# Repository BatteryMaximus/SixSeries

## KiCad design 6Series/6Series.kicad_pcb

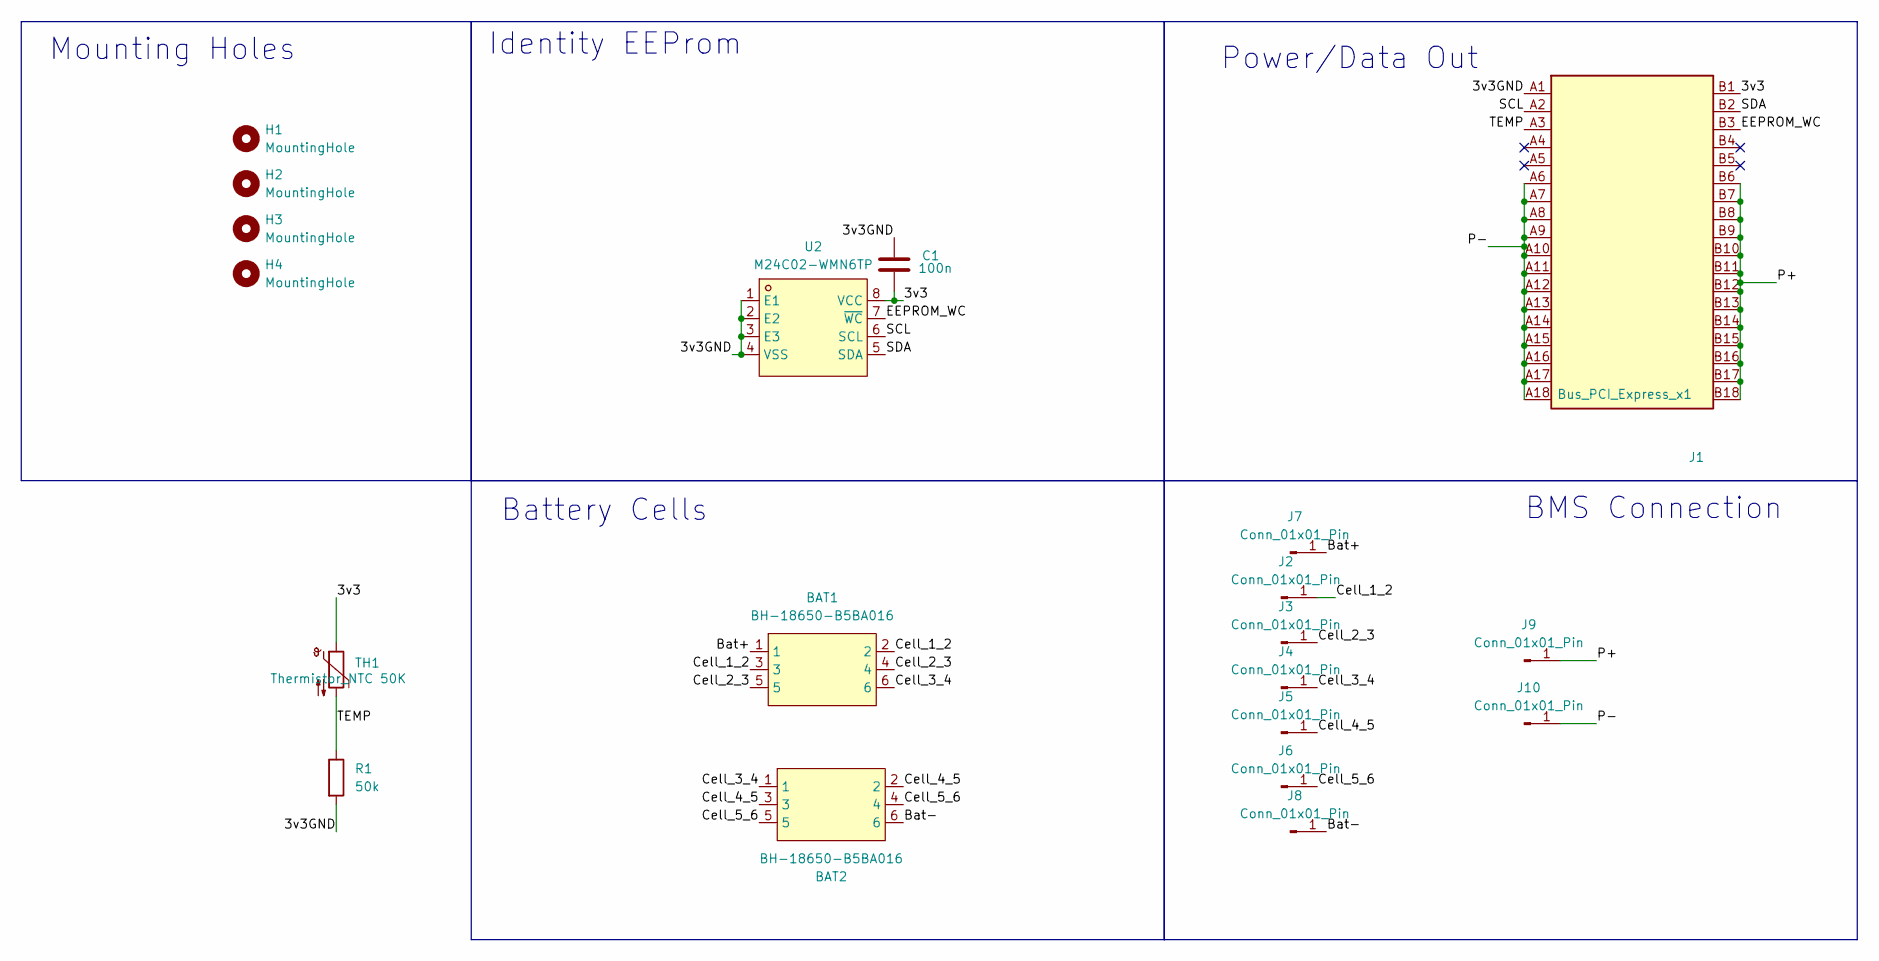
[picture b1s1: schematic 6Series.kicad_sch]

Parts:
BAT1, BAT2: BH-18650-B5BA016; BAT-SMD_BH-18650-B5BA016; LCSC Part C19184086
C1: 100n; C_1206_3216Metric_Pad1.33x1.80mm_HandSolder
H1, H2, H3, H4: MountingHole; MountingHole_3.2mm_M3
J1: Bus_PCI_Express_x1; BUS_PCIexpress_x1
J2, J3, J4, J5, J6, J7, J8, J9, J10: Conn_01x01_Pin; TestPoint_Pad_4.0x4.0mm
R1: 50k; R_1206_3216Metric_Pad1.30x1.75mm_HandSolder
TH1: Thermistor_NTC 50K; R_1206_3216Metric_Pad1.30x1.75mm_HandSolder
U2: M24C02-WMN6TP; SOIC-8_L4.9-W3.9-P1.27-LS6.0-BL; LCSC Part C7562

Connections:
/3v3: C1.2, J1.B1, TH1.1, U2.8 (VCC)
/3v3GND: C1.1, J1.A1, R1.2, U2.1 (E1), U2.2 (E2), U2.3 (E3), U2.4 (VSS)
/Bat+: BAT1.1, J7.1
/Bat-: BAT2.6, J8.1
/Cell_1_2: BAT1.2, BAT1.3, J2.1
/Cell_2_3: BAT1.4, BAT1.5, J3.1
/Cell_3_4: BAT1.6, BAT2.1, J4.1
/Cell_4_5: BAT2.2, BAT2.3, J5.1
/Cell_5_6: BAT2.4, BAT2.5, J6.1
/EEPROM_WC: J1.B3, U2.7 (~WC)
/P+: J1.B6, J1.B7, J1.B8, J1.B9, J1.B10, J1.B11, J1.B12, J1.B13, J1.B14, J1.B15, J1.B16, J1.B17, J1.B18, J9.1
/P-: J1.A6, J1.A7, J1.A8, J1.A9, J1.A10, J1.A11, J1.A12, J1.A13, J1.A14, J1.A15, J1.A16, J1.A17, J1.A18, J10.1
/SCL: J1.A2, U2.6 (SCL)
/SDA: J1.B2, U2.5 (SDA)
/TEMP: J1.A3, R1.1, TH1.2

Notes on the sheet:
BMS Connection
Mounting Holes
Power/Data Out
Battery Cells
Identity EEProm

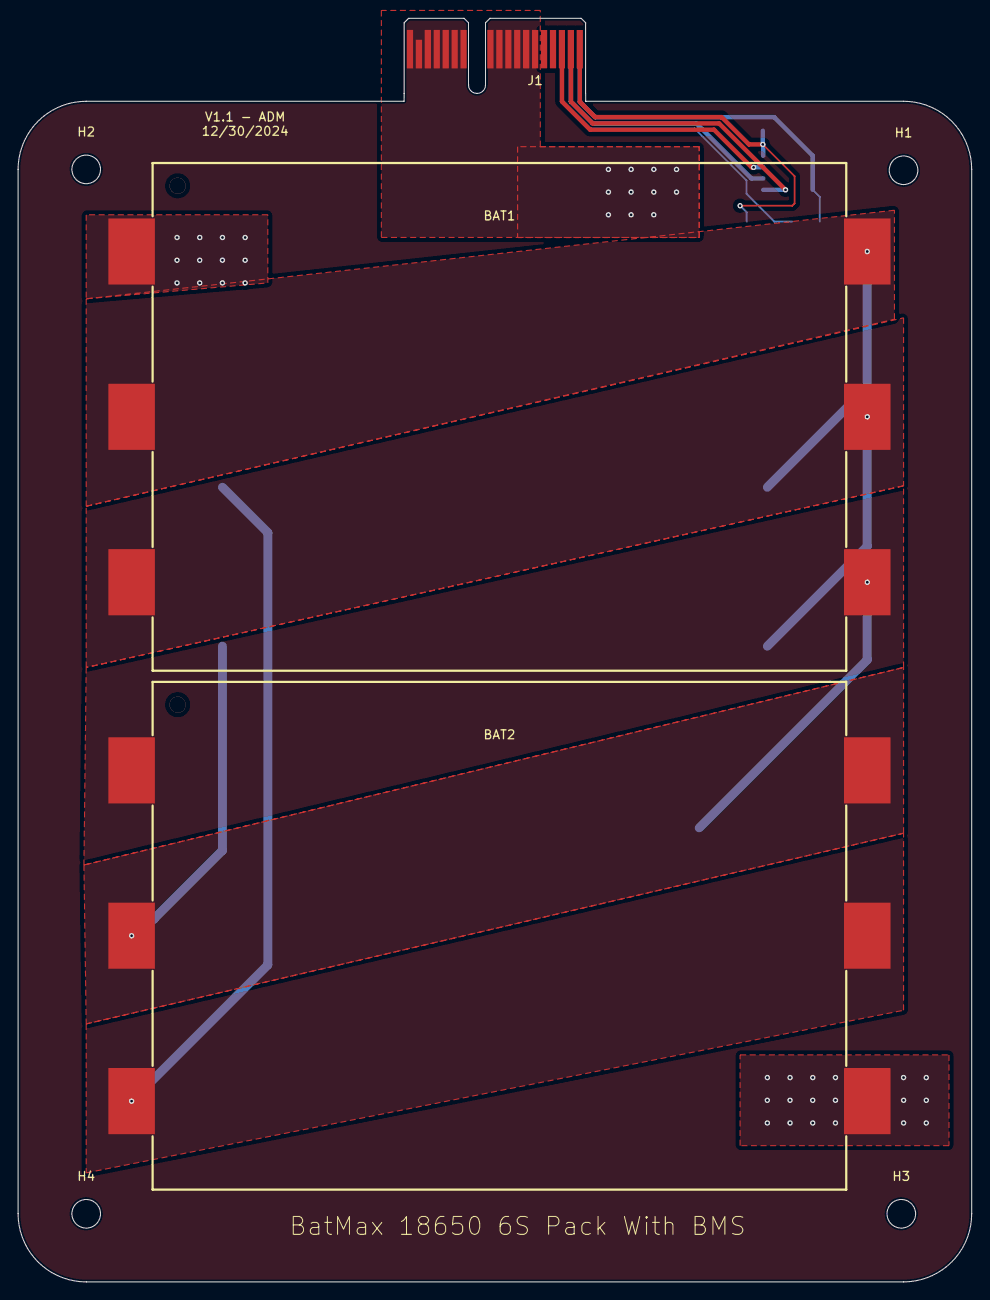
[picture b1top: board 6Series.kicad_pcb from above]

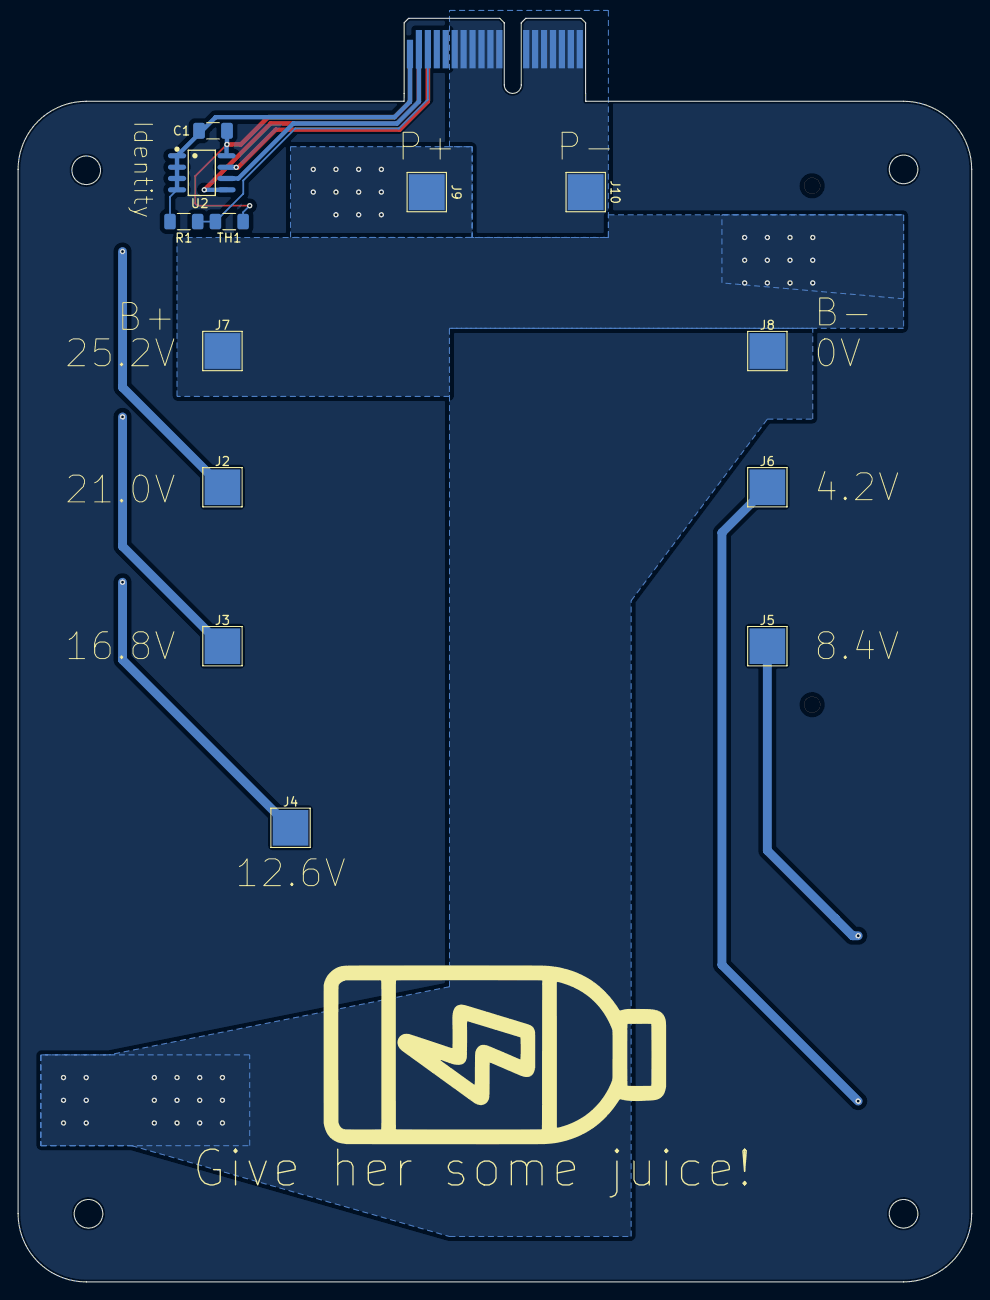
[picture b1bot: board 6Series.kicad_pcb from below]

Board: 2 copper layers, 106.7 x 141.4 mm, 20 parts (13 on the bottom side), 15 nets.

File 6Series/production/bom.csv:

Designator,Footprint,Quantity,Value,LCSC Part #
"BAT1, BAT2",BAT-SMD_BH-18650-B5BA016,2,BH-18650-B5BA016,
C1,1206,1,100n,
J1,BUS_PCIexpress_x1,1,Bus_PCI_Express_x1,
"J10, J2, J3, J4, J5, J6, J7, J8, J9",TestPoint_Pad_4.0x4.0mm,9,Conn_01x01_Pin,
U2,SOIC-8_L4.9-W3.9-P1.27-LS6.0-BL,1,M24C02-WMN6TP,

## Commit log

2025-04-01 Added PCB
